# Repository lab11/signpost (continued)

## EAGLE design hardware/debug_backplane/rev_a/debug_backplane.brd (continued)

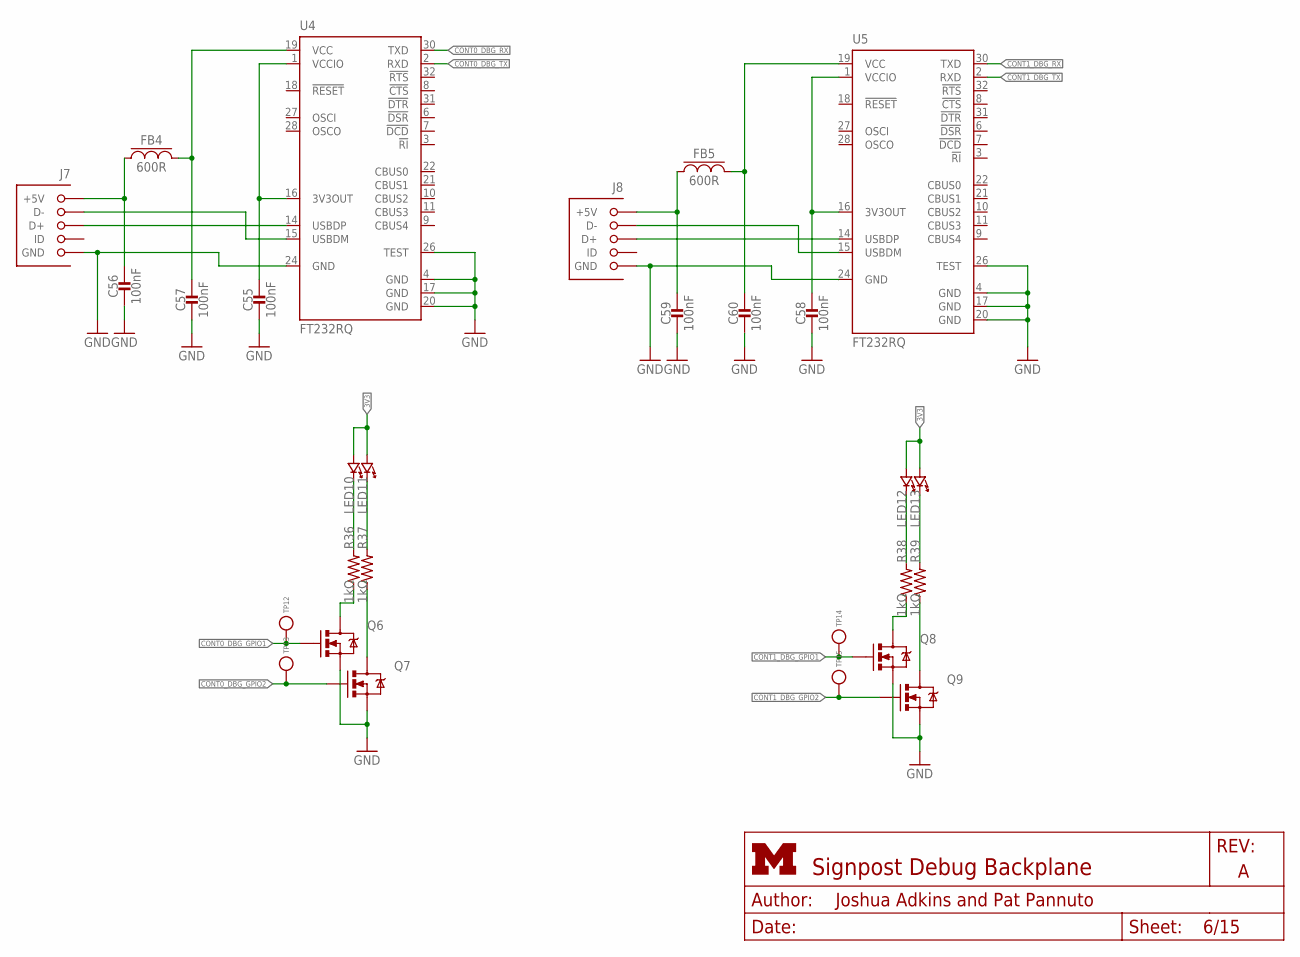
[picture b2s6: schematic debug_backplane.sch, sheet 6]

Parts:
C55, C56, C57, C58, C59, C60: 100nF; 0603_CAP
FB4, FB5: 600R; 0603_CAP
J7, J8: MICRO_USB_B_HIROSE_ZX62R-B-5P; USB_MICRO_B-HIROSE-ZX62R-B-5P
LED10, LED11, LED12, LED13: LED0603; LED-0603
Q6, Q7, Q8, Q9: MOSFET-NCHANNELSMD; SOT23-3
R36, R37, R38, R39: 1kΩ; 0603-RES
TP12, TP13, TP14, TP15: TEST_POINT_0.040IN; TESTPOINT_0.040IN
U4, U5: FT232RQ; QFN32

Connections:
3V3: LED10.A (ANODE), LED11.A (ANODE), LED12.A (ANODE), LED13.A (ANODE); also elsewhere on the board
CONT0_DBG_GPIO1: Q6.1 (G), TP12.TESTPOINT; also elsewhere on the board
CONT0_DBG_GPIO2: Q7.1 (G), TP13.TESTPOINT; also elsewhere on the board
CONT0_DBG_RX: U4.30 (TXD); also elsewhere on the board
CONT0_DBG_TX: U4.2 (RXD); also elsewhere on the board
CONT0_VCCIO: C55.1, U4.1 (VCCIO), U4.16 (3V3OUT)
CONT1_DBG_GPIO1: Q8.1 (G), TP14.TESTPOINT; also elsewhere on the board
CONT1_DBG_GPIO2: Q9.1 (G), TP15.TESTPOINT; also elsewhere on the board
CONT1_DBG_RX: U5.30 (TXD); also elsewhere on the board
CONT1_DBG_TX: U5.2 (RXD); also elsewhere on the board
CONT1_VCCIO: C58.1, U5.1 (VCCIO), U5.16 (3V3OUT)
GND: C55.2, C56.2, C57.2, C58.2, C59.2, C60.2, J7.5 (GND), J8.5 (GND), Q6.2 (S), Q7.2 (S), Q8.2 (S), Q9.2 (S), U4.4 (GND), U4.17 (GND), U4.20 (GND), U4.24 (GND), U4.26 (TEST), U5.4 (GND), U5.17 (GND), U5.20 (GND), U5.24 (GND), U5.26 (TEST); also elsewhere on the board
unnamed: J7.2 (D-), U4.15 (USBDM)
unnamed: J7.3 (D+), U4.14 (USBDP)
unnamed: C56.1, FB4.1, J7.1 (+5V)
unnamed: C57.1, FB4.2, U4.19 (VCC)
unnamed: J8.2 (D-), U5.15 (USBDM)
unnamed: J8.3 (D+), U5.14 (USBDP)
unnamed: C59.1, FB5.1, J8.1 (+5V)
unnamed: C60.1, FB5.2, U5.19 (VCC)
unnamed: LED10.C (CATHODE), R36.2
unnamed: LED11.C (CATHODE), R37.2
unnamed: Q6.3 (D), R36.1
unnamed: Q7.3 (D), R37.1
unnamed: LED12.C (CATHODE), R38.2
unnamed: LED13.C (CATHODE), R39.2
unnamed: Q8.3 (D), R38.1
unnamed: Q9.3 (D), R39.1

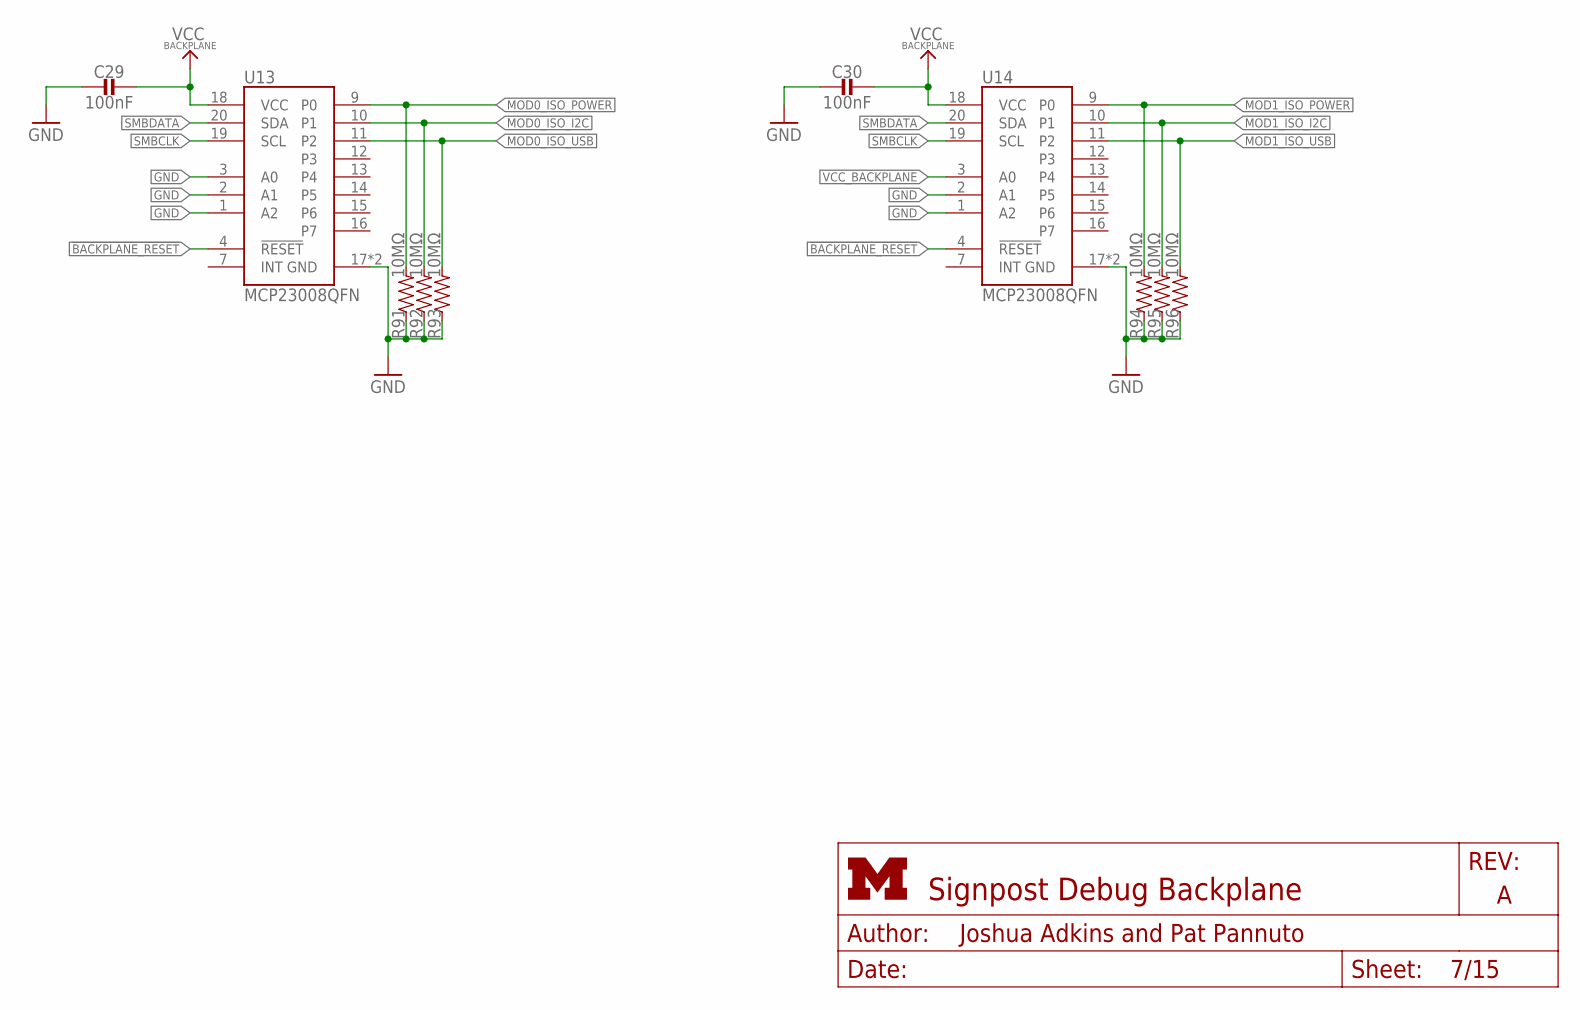
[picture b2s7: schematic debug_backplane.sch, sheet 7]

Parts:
C29, C30: 100nF; 0603_CAP
R91, R92, R93, R94, R95, R96: 10MΩ; 0603-RES
U13, U14: MCP23008QFN; QFN-20-4MM

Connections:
!BACKPLANE_RESET: U13.4 (!RESET), U14.4 (!RESET); also elsewhere on the board
GND: C29.2, C30.2, R91.1, R92.1, R93.1, R94.1, R95.1, R96.1, U13.1 (A2), U13.2 (A1), U13.3 (A0), U13.17 (GND), U13.GND, U14.1 (A2), U14.2 (A1), U14.17 (GND), U14.GND; also elsewhere on the board
MOD0_ISO_I2C: R92.2, U13.10 (P1); also elsewhere on the board
MOD0_ISO_POWER: R91.2, U13.9 (P0); also elsewhere on the board
MOD0_ISO_USB: R93.2, U13.11 (P2); also elsewhere on the board
MOD1_ISO_I2C: R95.2, U14.10 (P1); also elsewhere on the board
MOD1_ISO_POWER: R94.2, U14.9 (P0); also elsewhere on the board
MOD1_ISO_USB: R96.2, U14.11 (P2); also elsewhere on the board
SMBCLK: U13.19 (SCL), U14.19 (SCL); also elsewhere on the board
SMBDATA: U13.20 (SDA), U14.20 (SDA); also elsewhere on the board
VCC_BACKPLANE: C29.1, C30.1, U13.18 (VCC), U14.3 (A0), U14.18 (VCC); also elsewhere on the board

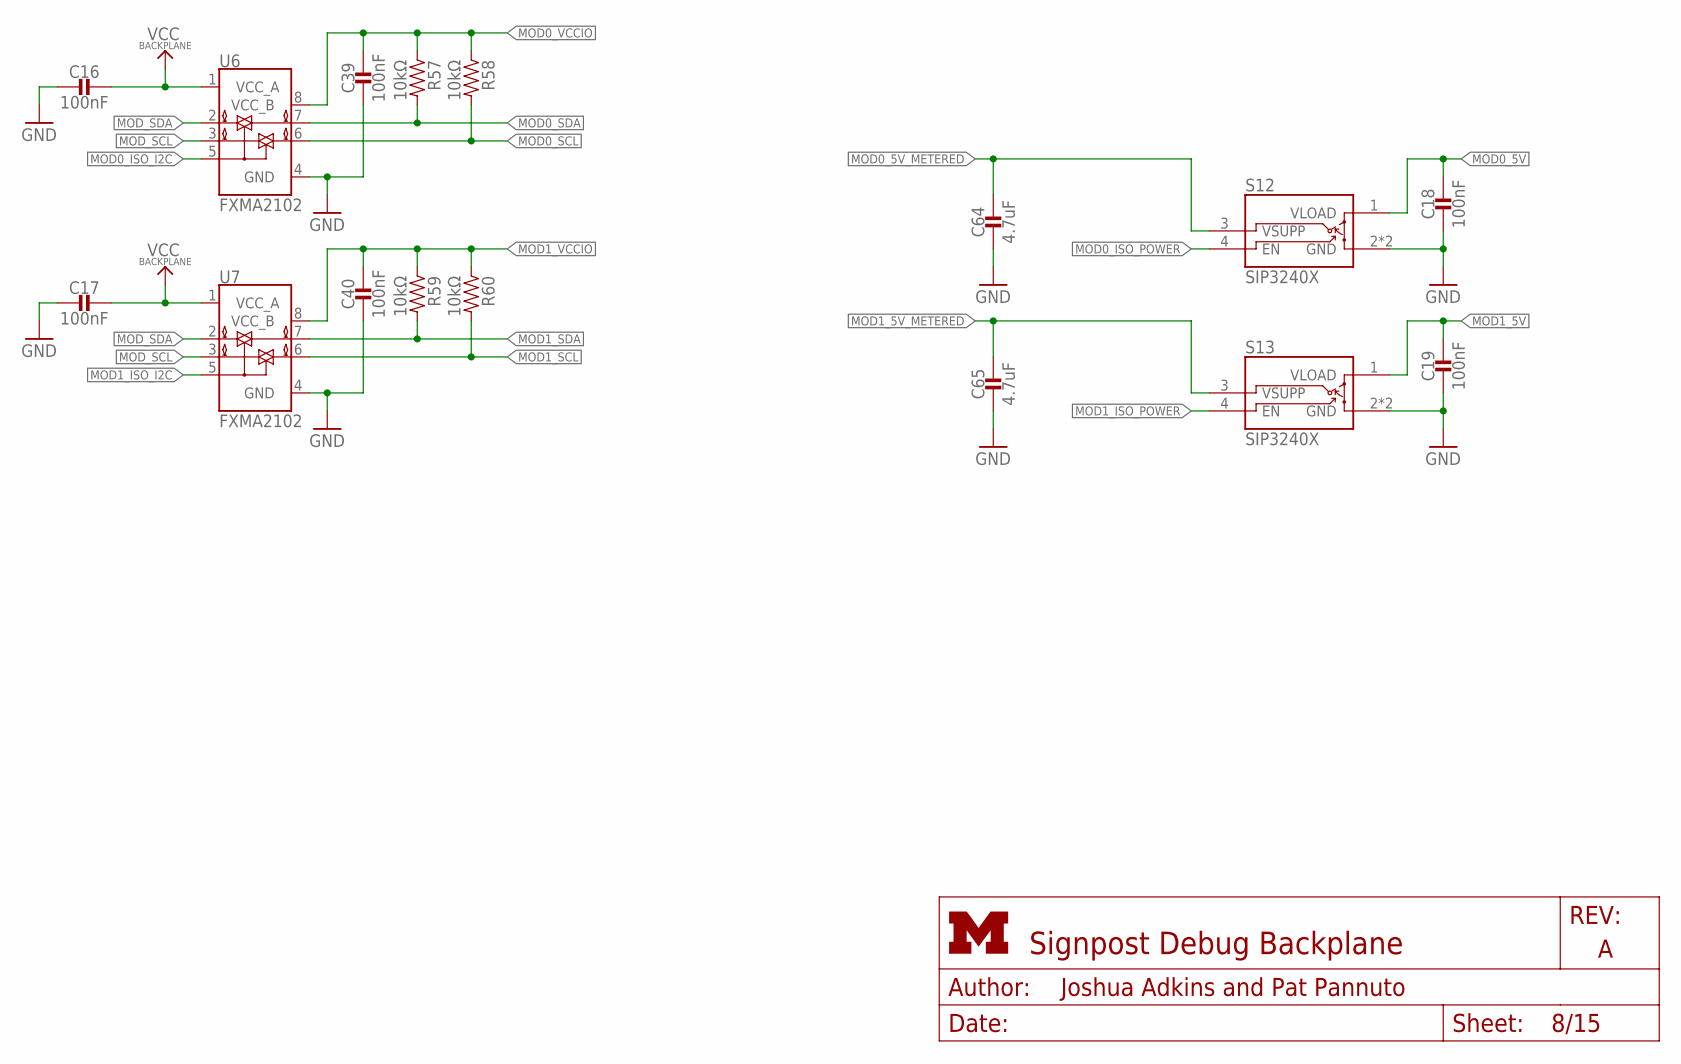
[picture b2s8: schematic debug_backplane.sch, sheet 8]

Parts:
C16, C17, C18, C19, C39, C40: 100nF; 0603_CAP
C64, C65: 4.7uF; 0603_CAP
R57, R58, R59, R60: 10kΩ; 0603-RES
S12, S13: SIP3240X; TDFN4
U6, U7: FXMA2102; UMLP-8

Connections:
GND: C16.2, C17.2, C18.2, C19.2, C39.2, C40.2, C64.2, C65.2, S12.2 (GND), S12.PAD (GND), S13.2 (GND), S13.PAD (GND), U6.4 (GND), U7.4 (GND); also elsewhere on the board
MOD0_5V: C18.1, S12.1 (VLOAD); also elsewhere on the board
MOD0_5V_METERED: C64.1, S12.3 (VSUPP); also elsewhere on the board
MOD0_ISO_I2C: U6.5 (OE); also elsewhere on the board
MOD0_ISO_POWER: S12.4 (EN); also elsewhere on the board
MOD0_SCL: R58.2, U6.6 (B1); also elsewhere on the board
MOD0_SDA: R57.2, U6.7 (B0); also elsewhere on the board
MOD0_VCCIO: C39.1, R57.1, R58.1, U6.8 (VCC_B); also elsewhere on the board
MOD1_5V: C19.1, S13.1 (VLOAD); also elsewhere on the board
MOD1_5V_METERED: C65.1, S13.3 (VSUPP); also elsewhere on the board
MOD1_ISO_I2C: U7.5 (OE); also elsewhere on the board
MOD1_ISO_POWER: S13.4 (EN); also elsewhere on the board
MOD1_SCL: R60.2, U7.6 (B1); also elsewhere on the board
MOD1_SDA: R59.2, U7.7 (B0); also elsewhere on the board
MOD1_VCCIO: C40.1, R59.1, R60.1, U7.8 (VCC_B); also elsewhere on the board
MOD_SCL: U6.3 (A1), U7.3 (A1); also elsewhere on the board
MOD_SDA: U6.2 (A0), U7.2 (A0); also elsewhere on the board
VCC_BACKPLANE: C16.1, C17.1, U6.1 (VCC_A), U7.1 (VCC_A); also elsewhere on the board

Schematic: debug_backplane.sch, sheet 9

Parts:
C20, C21, C22, C23, C24, C25, C26, C27: 100nF; 0603_CAP
U17, U18, U19, U20: SN74LVC2T45; VFSOP-8

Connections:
CONT_MOD0_IN: U17.2 (A1); also elsewhere on the board
CONT_MOD0_OUT: U19.2 (A1); also elsewhere on the board
CONT_MOD1_IN: U18.2 (A1); also elsewhere on the board
CONT_MOD1_OUT: U20.2 (A1); also elsewhere on the board
GND: C20.2, C21.2, C22.2, C23.2, C24.2, C25.2, C26.2, C27.2, U17.4 (GND), U18.4 (GND), U19.4 (GND), U19.5 (DIR), U20.4 (GND), U20.5 (DIR); also elsewhere on the board
MOD0_IN: U17.7 (B1); also elsewhere on the board
MOD0_OUT: U19.7 (B1); also elsewhere on the board
MOD0_PPS: U17.6 (B2); also elsewhere on the board
MOD0_VCCIO: C24.1, C26.1, U17.8 (VCC_B), U19.8 (VCC_B); also elsewhere on the board
MOD1_IN: U18.7 (B1); also elsewhere on the board
MOD1_OUT: U20.7 (B1); also elsewhere on the board
MOD1_PPS: U18.6 (B2); also elsewhere on the board
MOD1_VCCIO: C25.1, C27.1, U18.8 (VCC_B), U20.8 (VCC_B); also elsewhere on the board
PPS: U17.3 (A2), U18.3 (A2); also elsewhere on the board
VCC_BACKPLANE: C20.1, C21.1, C22.1, C23.1, U17.1 (VCC_A), U17.5 (DIR), U18.1 (VCC_A), U18.5 (DIR), U19.1 (VCC_A), U20.1 (VCC_A); also elsewhere on the board

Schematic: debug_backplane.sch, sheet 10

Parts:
C3, C4: 22pF; 0603_CAP; DIGIKEY 1276-1023-1-ND
C28: 100nF; 0603_CAP
C66: 4.7uF; 0603_CAP
R40, R41: 1.5kΩ; 0603-RES
R66, R67, R68, R69, R72: 10kΩ; 0603-RES
R79, R80, R81, R82, R83, R84, R85, R86: 15kΩ; 0603-RES
U24: TUSB2077A; LQFP-48
Y1: ABMM

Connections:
!BACKPLANE_RESET: U24.6 (!RESET); also elsewhere on the board
GND: C3.1, C4.1, C28.1, C66.1, R79.2, R80.2, R81.2, R82.2, R83.2, R84.2, R85.2, R86.2, U24.5 (GND), U24.10 (!BUSPWR), U24.24 (GND), U24.43 (GND), U24.48 (MODE); also elsewhere on the board
HUB_!OVRCUR1: U24.12 (!OVRCUR1); also elsewhere on the board
HUB_!OVRCUR2: U24.16 (!OVRCUR2); also elsewhere on the board
HUB_!OVRCUR3: R72.1, U24.20 (!OVRCUR3); also elsewhere on the board
HUB_!OVRCUR4: R67.1, U24.25 (!OVRCUR4)
HUB_!OVRCUR5: R66.1, U24.29 (!OVRCUR5)
HUB_!OVRCUR6: R68.1, U24.33 (!OVRCUR6)
HUB_!OVRCUR7: R69.1, U24.37 (!OVRCUR7)
HUB_!PWRON1: U24.11 (!PWRON1); also elsewhere on the board
HUB_!PWRON2: U24.15 (!PWRON2); also elsewhere on the board
HUB_!PWRON3: U24.19 (!PWRON3); also elsewhere on the board
HUB_!PWRON4: U24.23 (!PWRON4)
HUB_!PWRON5: U24.28 (!PWRON5)
HUB_!PWRON6: U24.32 (!PWRON6)
HUB_!PWRON7: U24.36 (!PWRON7)
HUB_CFG: U24.40 (HUBCFG); also elsewhere on the board
HUB_DM1: U24.13 (DM1); also elsewhere on the board
HUB_DM2: U24.17 (DM2); also elsewhere on the board
HUB_DM3: U24.21 (DM3); also elsewhere on the board
HUB_DM4: R82.1, U24.26 (DM4)
HUB_DM5: R80.1, U24.30 (DM5)
HUB_DM6: R84.1, U24.34 (DM6)
HUB_DM7: R86.1, U24.38 (DM7)
HUB_DP1: U24.14 (DP1); also elsewhere on the board
HUB_DP2: U24.18 (DP2); also elsewhere on the board
HUB_DP3: U24.22 (DP3); also elsewhere on the board
HUB_DP4: R81.1, U24.27 (DP4)
HUB_DP5: R79.1, U24.31 (DP5)
HUB_DP6: R83.1, U24.35 (DP6)
HUB_DP7: R85.1, U24.39 (DP7)
HUB_PORTDIS: U24.42 (PORTDIS); also elsewhere on the board
HUB_PORTPWR: U24.41 (PORTPWR); also elsewhere on the board
unnamed: R40.2, U24.2 (DP0PUR)
unnamed: C4.2, R41.1, Y1.1
unnamed: C3.2, U24.45 (XTAL1), Y1.3 (2)
unnamed: R41.2, U24.44 (XTAL2)
USB+: R40.1, U24.3 (DP0); also elsewhere on the board
USB-: U24.4 (DM0); also elsewhere on the board
USB_SUSPEND_STATUS: U24.1 (SUSPND); also elsewhere on the board
VCC_BACKPLANE: C28.2, C66.2, R66.2, R67.2, R68.2, R69.2, R72.2, U24.8 (EEDATA/!GANGED), U24.9 (VCC), U24.46 (VCC), U24.47 (!EXTMEM); also elsewhere on the board

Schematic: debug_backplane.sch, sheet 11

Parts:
C61: 100nF; 0603_CAP
J9: MICRO_USB_B_HIROSE_ZX62R-B-5P; USB_MICRO_B-HIROSE-ZX62R-B-5P
Q1: DMN32D2LDF; SOT353
R89, R90: 100kΩ; 0603-RES
U23: TS3USB30E; UQFN-10

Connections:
CONT_USB+: U23.2 (D2+); also elsewhere on the board
CONT_USB-: U23.6 (D2-); also elsewhere on the board
GND: C61.1, J9.5 (GND), Q1.S, R90.1, U23.4 (GND), U23.8 (!OE); also elsewhere on the board
unnamed: J9.1 (+5V), Q1.G2, R90.2
unnamed: Q1.D2, R89.1, U23.10 (S)
unnamed: J9.3 (D+), U23.1 (D1+)
unnamed: J9.2 (D-), U23.7 (D1-)
USB+: U23.3 (D+); also elsewhere on the board
USB-: U23.5 (D-); also elsewhere on the board
VCC_BACKPLANE: C61.2, R89.2, U23.9 (VCC); also elsewhere on the board

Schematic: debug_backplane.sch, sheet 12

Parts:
C5, C6, C7, C8, C9, C10: 22pF; 0402_CAP
C37, C38: 100nF; 0603_CAP
D7, D8: SN75240-TSSOP; TSSOP-8
R6, R7, R8, R9, R10, R11: 27Ω; 0402_RES-HIGH_SPEED
R12, R13, R14, R15: 50Ω; 0603-RES
R73, R74, R75, R76, R77, R78: 15kΩ; 0603-RES
U21, U22: TS3USB30E; UQFN-10

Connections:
GND: C5.2, C6.2, C7.2, C8.2, C9.2, C10.2, C37.1, C38.1, D7.1 (GND), D7.3 (GND), D7.5 (GND), D7.7 (GND), D8.1 (GND), D8.3 (GND), D8.5 (GND), D8.7 (GND), R12.2, R13.2, R14.2, R15.2, R73.1, R74.1, R75.1, R76.1, R77.1, R78.1, U21.4 (GND), U21.10 (S), U22.4 (GND), U22.10 (S); also elsewhere on the board
HUB_DM1: C8.1, R9.2; also elsewhere on the board
HUB_DM2: C6.1, R7.2; also elsewhere on the board
HUB_DM3: C10.1, R11.2; also elsewhere on the board
HUB_DP1: C7.1, R8.2; also elsewhere on the board
HUB_DP2: C5.1, R6.2; also elsewhere on the board
HUB_DP3: C9.1, R10.2; also elsewhere on the board
MOD0_D+_HUB-SW: D8.4 (D), R6.1, R73.2, U21.3 (D+)
MOD0_D-_HUB-SW: D8.2 (C), R7.1, R74.2, U21.5 (D-)
MOD0_USB+: U21.1 (D1+); also elsewhere on the board
MOD0_USB-: U21.7 (D1-); also elsewhere on the board
MOD0_USB_!EN: U21.8 (!OE); also elsewhere on the board
MOD1_D+_HUB-SW: D8.8 (A), R8.1, R75.2, U22.3 (D+)
MOD1_D-_HUB-SW: D8.6 (B), R9.1, R76.2, U22.5 (D-)
MOD1_USB+: U22.1 (D1+); also elsewhere on the board
MOD1_USB-: U22.7 (D1-); also elsewhere on the board
MOD1_USB_!EN: U22.8 (!OE); also elsewhere on the board
MOD2_USB+: D7.8 (A), R10.1, R77.2; also elsewhere on the board
MOD2_USB-: D7.6 (B), R11.1, R78.2; also elsewhere on the board
unnamed: R12.1, U21.2 (D2+)
unnamed: R15.1, U22.6 (D2-)
unnamed: R14.1, U22.2 (D2+)
unnamed: R13.1, U21.6 (D2-)
VCC_BACKPLANE: C37.2, C38.2, U21.9 (VCC), U22.9 (VCC); also elsewhere on the board

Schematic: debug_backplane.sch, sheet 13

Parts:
C31, C32, C33, C34, C35, C36: 100nF; 0603_CAP
C68, C69: 150uF; 1210_CAP; DIGIKEY 1276-3367-1-ND
R55, R56: 10kΩ; 0603-RES
S1, S2: AP2401MP; MSOP-8EP
S9, S10: NC7SZ157; SC70-6

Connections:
GND: C31.2, C32.2, C33.2, C34.2, C35.2, C36.2, C68.2, C69.2, S1.1 (GND), S1.PAD (GND), S2.1 (GND), S2.PAD (GND), S9.2 (GND), S10.2 (GND); also elsewhere on the board
HUB_!OVRCUR1: R56.1, S2.5 (!FLG); also elsewhere on the board
HUB_!OVRCUR2: R55.1, S1.5 (!FLG); also elsewhere on the board
HUB_!PWRON1: S10.1 (I1); also elsewhere on the board
HUB_!PWRON2: S9.1 (I1); also elsewhere on the board
MOD0_5V_METERED: C35.1, S1.2 (IN), S1.3 (IN); also elsewhere on the board
MOD0_ISO_USB: S9.6 (S); also elsewhere on the board
MOD0_USB_!EN: S1.4 (!EN), S9.4 (Z); also elsewhere on the board
MOD0_USB_VBUS: C31.1, C68.1, S1.6 (OUT), S1.7 (OUT); also elsewhere on the board
MOD1_5V_METERED: C36.1, S2.2 (IN), S2.3 (IN); also elsewhere on the board
MOD1_ISO_USB: S10.6 (S); also elsewhere on the board
MOD1_USB_!EN: S2.4 (!EN), S10.4 (Z); also elsewhere on the board
MOD1_USB_VBUS: C32.1, C69.1, S2.6 (OUT), S2.7 (OUT); also elsewhere on the board
VCC_BACKPLANE: C33.1, C34.1, R55.2, R56.2, S9.3 (I0), S9.5 (VCC), S10.3 (I0), S10.5 (VCC); also elsewhere on the board

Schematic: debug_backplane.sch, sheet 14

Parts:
C1, C2: 8pF; 0603_CAP; DIGIKEY 490-8230-1-ND
C41, C42, C43, C44, C46, C47, C48: 100nF; 0603_CAP; DIGIKEY 490-10777-1-ND
C45: 100nF; 0402_CAP; DIGIKEY 490-10777-1-ND
C67: 4.7uF; 0402_CAP; DIGIKEY 490-13252-1-ND
FB1: 600R; 0603_CAP
FB6: 1.5kR; 0603_CAP; DIGIKEY 490-5216-1-ND
J4: MICRO_USB_B_HIROSE_ZX62R-B-5P; USB_MICRO_B-HIROSE-ZX62R-B-5P
L1: 22uH; 1212
R1: 0Ω; 0603-RES; DIGIKEY 1276-3431-1-ND
R71: 10kΩ; 0603-RES; DIGIKEY 1276-3431-1-ND
R87, R88: 100kΩ; 0603-RES; DIGIKEY 1276-3432-1-ND
S3: B3U-1000P
TP54: TEST_POINT_0.040IN; TESTPOINT_0.040IN
U1: FT232RQ; QFN32
U16: SAM4LC8AA; QFN-48-7MM
X1: 16MHz; FHXXX

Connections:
3V3: C42.1, C43.1, C44.1, FB6.2, R71.2, R87.2, R88.2, U16.8 (VDDIN), U16.27 (VLCD), U16.31 (VLCDIN), U16.40 (VDDIO), U16.45 (VDDIO); also elsewhere on the board
CONTROLLER_BUCK/LDO_N: R1.2, R71.1, U16.3 (PA02)
CONTROLLER_XIN: C1.1, U16.1 (PA00), X1.3 (2)
CONTROLLER_XOUT: C2.1, U16.2 (PA01), X1.1
CONT_MOD2_IN: U16.39 (PA20); also elsewhere on the board
CONT_MOD2_OUT: U16.38 (PA19); also elsewhere on the board
GND: C1.2, C2.2, C41.2, C42.2, C43.2, C44.2, C45.2, C46.2, C47.2, C48.2, C67.2, J4.5 (GND), R1.1, S3.1, TP54.TESTPOINT, U1.4 (GND), U1.17 (GND), U1.20 (GND), U1.24 (GND), U1.26 (TEST), U16.6 (GND), U16.17 (GNDANA), U16.30 (GND), U16.48 (GND), U16.THERMAL (GND), X1.2 (GND), X1.4 (GND); also elsewhere on the board
MOD2_USB+: U16.47 (PA26); also elsewhere on the board
MOD2_USB-: U16.46 (PA25); also elsewhere on the board
MOD_SCL: U16.44 (PA24); also elsewhere on the board
MOD_SDA: U16.43 (PA23); also elsewhere on the board
unnamed: C41.1, FB6.1, U16.19 (VDDANA)
unnamed: L1.P$2 (2), U16.5 (VDDCORE)
unnamed: U16.28 (BIASH), U16.29 (BIASL)
unnamed: U16.25 (CAPH), U16.26 (CAPL)
unnamed: J4.2 (D-), U1.15 (USBDM)
unnamed: C45.1, C67.1, L1.P$1 (1), U16.7 (VDDOUT)
unnamed: J4.3 (D+), U1.14 (USBDP)
unnamed: C46.1, FB1.2, J4.1 (+5V)
unnamed: C47.1, FB1.1, U1.19 (VCC)
unnamed: C48.1, U1.1 (VCCIO), U1.16 (3V3OUT)
PPS: U16.37 (PA18); also elsewhere on the board
RADIO_!RESET: S3.2, U16.4 (!RESET); also elsewhere on the board
RADIO_RX: U1.30 (TXD), U16.23 (PA11)
RADIO_SWDCLK: R88.1, U16.9 (TCK); also elsewhere on the board
RADIO_SWDIO: R87.1, U16.10 (PA03); also elsewhere on the board
RADIO_TX: U1.2 (RXD), U16.24 (PA12)

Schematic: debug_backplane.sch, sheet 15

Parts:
D1, D2, D3, D4, D5, D6: LED0603; LED-0603
R16, R17, R18, R19, R20, R21: 1kΩ; 0603-RES
TP1, TP2, TP3, TP4, TP5, TP6, TP7, TP8, TP9, TP10, TP11, TP16, TP17, TP18, TP20, TP23, TP24, TP25, TP27, TP28, TP29, TP30, TP31, TP32, TP33, TP34, TP35, TP36, TP37, TP41, TP42, TP43, TP44, TP45, TP46, TP47, TP48, TP49, TP50, TP51, TP52, TP53, TP55, TP56, TP57, TP58, TP1001, TP1002, TP1003, TP1004, TP1005, TP1006: TEST_POINT_0.040IN; TESTPOINT_0.040IN

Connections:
3V3: TP7.TESTPOINT; also elsewhere on the board
5V: TP4.TESTPOINT; also elsewhere on the board
!BACKPLANE_RESET: TP9.TESTPOINT; also elsewhere on the board
!SMBALERT: TP3.TESTPOINT; also elsewhere on the board
GND: R16.1, R17.1, R18.1, R19.1, R20.1, R21.1, TP11.TESTPOINT, TP25.TESTPOINT, TP27.TESTPOINT, TP51.TESTPOINT, TP56.TESTPOINT; also elsewhere on the board
HUB_!OVRCUR1: TP33.TESTPOINT; also elsewhere on the board
HUB_!OVRCUR2: TP35.TESTPOINT; also elsewhere on the board
HUB_!OVRCUR3: TP37.TESTPOINT; also elsewhere on the board
HUB_!PWRON1: TP32.TESTPOINT; also elsewhere on the board
HUB_!PWRON2: TP34.TESTPOINT; also elsewhere on the board
HUB_!PWRON3: TP36.TESTPOINT; also elsewhere on the board
HUB_CFG: TP28.TESTPOINT; also elsewhere on the board
HUB_PORTDIS: TP30.TESTPOINT; also elsewhere on the board
HUB_PORTPWR: TP29.TESTPOINT; also elsewhere on the board
MOD0_5V: TP57.TESTPOINT; also elsewhere on the board
MOD0_5V_METERED: TP16.TESTPOINT; also elsewhere on the board
MOD0_IN: TP48.TESTPOINT; also elsewhere on the board
MOD0_ISO_I2C: D2.A (ANODE), TP1002.TESTPOINT; also elsewhere on the board
MOD0_ISO_POWER: D1.A (ANODE), TP1001.TESTPOINT; also elsewhere on the board
MOD0_ISO_USB: D3.A (ANODE), TP1003.TESTPOINT; also elsewhere on the board
MOD0_OUT: TP49.TESTPOINT; also elsewhere on the board
MOD0_PPS: TP46.TESTPOINT; also elsewhere on the board
MOD0_SCL: TP43.TESTPOINT; also elsewhere on the board
MOD0_SDA: TP42.TESTPOINT; also elsewhere on the board
MOD0_USB_VBUS: TP20.TESTPOINT; also elsewhere on the board
MOD0_VCCIO: TP50.TESTPOINT; also elsewhere on the board
MOD1_5V: TP58.TESTPOINT; also elsewhere on the board
MOD1_5V_METERED: TP17.TESTPOINT; also elsewhere on the board
MOD1_IN: TP52.TESTPOINT; also elsewhere on the board
MOD1_ISO_I2C: D5.A (ANODE), TP1005.TESTPOINT; also elsewhere on the board
MOD1_ISO_POWER: D4.A (ANODE), TP1004.TESTPOINT; also elsewhere on the board
MOD1_ISO_USB: D6.A (ANODE), TP1006.TESTPOINT; also elsewhere on the board
MOD1_OUT: TP53.TESTPOINT; also elsewhere on the board
MOD1_PPS: TP47.TESTPOINT; also elsewhere on the board
MOD1_SCL: TP45.TESTPOINT; also elsewhere on the board
MOD1_SDA: TP44.TESTPOINT; also elsewhere on the board
MOD1_USB_VBUS: TP41.TESTPOINT; also elsewhere on the board
MOD1_VCCIO: TP55.TESTPOINT; also elsewhere on the board
MOD_SCL: TP6.TESTPOINT; also elsewhere on the board
MOD_SDA: TP5.TESTPOINT; also elsewhere on the board
unnamed: D1.C (CATHODE), R16.2
unnamed: D2.C (CATHODE), R18.2
unnamed: D3.C (CATHODE), R17.2
unnamed: D4.C (CATHODE), R19.2
unnamed: D5.C (CATHODE), R20.2
unnamed: D6.C (CATHODE), R21.2
PPS: TP10.TESTPOINT; also elsewhere on the board
SMBCLK: TP2.TESTPOINT; also elsewhere on the board
SMBDATA: TP1.TESTPOINT; also elsewhere on the board
USB_SUSPEND_STATUS: TP31.TESTPOINT; also elsewhere on the board
VCC_BACKPLANE: TP8.TESTPOINT, TP24.TESTPOINT; also elsewhere on the board
VCC_LINUX: TP18.TESTPOINT, TP23.TESTPOINT; also elsewhere on the board

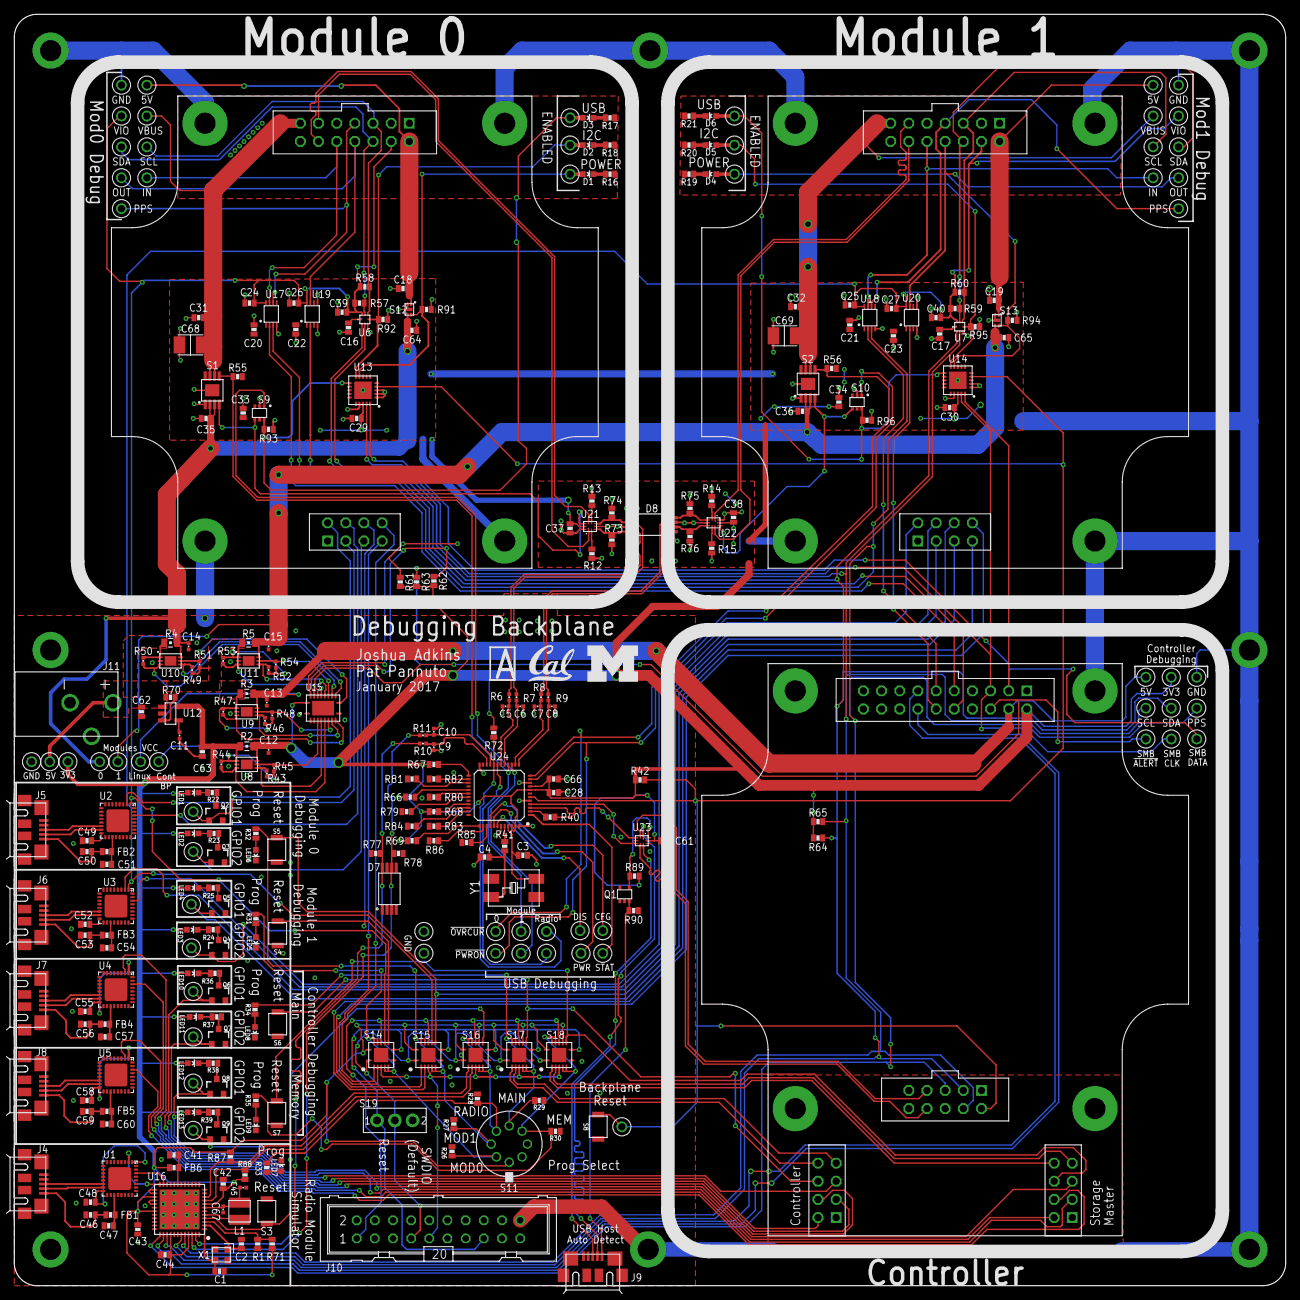
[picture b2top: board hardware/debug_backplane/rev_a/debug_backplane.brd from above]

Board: 2 copper layers, 177.8 x 177.8 mm, 321 parts (0 on the bottom side), 214 nets.

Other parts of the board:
U$12: UMICH_SOLID_200MIL
U$15: UCB_CAL_200MIL

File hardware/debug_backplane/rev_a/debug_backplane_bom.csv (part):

"# Bill of Materials",,,,,,,,,,,
"# Converted from debug_backplane_bom.xlsx",,,,,,,,,,,
"# Generated by bom_to_text.py",,,,,,,,,,,
"#",,,,,,,,,,,
Part,Value,Device,Package,Description,DIGIKEY,MF,MOUSER,MPN,NEWARK,OC_FARNELL,OC_NEWARK
C1,8pF,CAPACITOR0603_CAP,0603_CAP,0402 Capacitor,1276-2141-1-ND,,,,,,
C2,8pF,CAPACITOR0603_CAP,0603_CAP,0402 Capacitor,1276-2141-1-ND,,,,,,
C3,22pF,CAPACITOR0603_CAP,0603_CAP,0402 Capacitor,478-1167-1-ND,,,,,,
C4,22pF,CAPACITOR0603_CAP,0603_CAP,0402 Capacitor,478-1167-1-ND,,,,,,
C5,22pF,CAPACITOR0402_CAP,0402_CAP,0402 Capacitor,399-8827-1-ND,,,,,,
C6,22pF,CAPACITOR0402_CAP,0402_CAP,0402 Capacitor,399-8827-1-ND,,,,,,
C7,22pF,CAPACITOR0402_CAP,0402_CAP,0402 Capacitor,399-8827-1-ND,,,,,,
C8,22pF,CAPACITOR0402_CAP,0402_CAP,0402 Capacitor,399-8827-1-ND,,,,,,
C9,22pF,CAPACITOR0402_CAP,0402_CAP,0402 Capacitor,399-8827-1-ND,,,,,,
C10,22pF,CAPACITOR0402_CAP,0402_CAP,0402 Capacitor,399-8827-1-ND,,,,,,
C11,0.01uF,CAPACITOR0402_CAP,0402_CAP,0402 Capacitor,490-1313-1-ND,,,,,,
C12,0.1uF,CAPACITOR0402_CAP,0402_CAP,0402 Capacitor,478-1129-1-ND,,,,,,
C13,0.1uF,CAPACITOR0402_CAP,0402_CAP,0402 Capacitor,478-1129-1-ND,,,,,,
C14,0.1uF,CAPACITOR0402_CAP,0402_CAP,0402 Capacitor,478-1129-1-ND,,,,,,
C15,0.1uF,CAPACITOR0402_CAP,0402_CAP,0402 Capacitor,478-1129-1-ND,,,,,,
C16,100nF,CAPACITOR0603_CAP,0603_CAP,0402 Capacitor,490-1532-1-ND,,,,,,
C17,100nF,CAPACITOR0603_CAP,0603_CAP,0402 Capacitor,490-1532-1-ND,,,,,,
C18,100nF,CAPACITOR0603_CAP,0603_CAP,0402 Capacitor,490-1532-1-ND,,,,,,
C19,100nF,CAPACITOR0603_CAP,0603_CAP,0402 Capacitor,490-1532-1-ND,,,,,,
C20,100nF,CAPACITOR0603_CAP,0603_CAP,0402 Capacitor,490-1532-1-ND,,,,,,
C21,100nF,CAPACITOR0603_CAP,0603_CAP,0402 Capacitor,490-1532-1-ND,,,,,,
C22,100nF,CAPACITOR0603_CAP,0603_CAP,0402 Capacitor,490-1532-1-ND,,,,,,
C23,100nF,CAPACITOR0603_CAP,0603_CAP,0402 Capacitor,490-1532-1-ND,,,,,,
C24,100nF,CAPACITOR0603_CAP,0603_CAP,0402 Capacitor,490-1532-1-ND,,,,,,
C25,100nF,CAPACITOR0603_CAP,0603_CAP,0402 Capacitor,490-1532-1-ND,,,,,,
C26,100nF,CAPACITOR0603_CAP,0603_CAP,0402 Capacitor,490-1532-1-ND,,,,,,
C27,100nF,CAPACITOR0603_CAP,0603_CAP,0402 Capacitor,490-1532-1-ND,,,,,,
C28,100nF,CAPACITOR0603_CAP,0603_CAP,0402 Capacitor,490-1532-1-ND,,,,,,
C29,100nF,CAPACITOR0603_CAP,0603_CAP,0402 Capacitor,490-1532-1-ND,,,,,,
C30,100nF,CAPACITOR0603_CAP,0603_CAP,0402 Capacitor,490-1532-1-ND,,,,,,
C31,100nF,CAPACITOR0603_CAP,0603_CAP,0402 Capacitor,490-1532-1-ND,,,,,,
C32,100nF,CAPACITOR0603_CAP,0603_CAP,0402 Capacitor,490-1532-1-ND,,,,,,
C33,100nF,CAPACITOR0603_CAP,0603_CAP,0402 Capacitor,490-1532-1-ND,,,,,,
C34,100nF,CAPACITOR0603_CAP,0603_CAP,0402 Capacitor,490-1532-1-ND,,,,,,
C35,100nF,CAPACITOR0603_CAP,0603_CAP,0402 Capacitor,490-1532-1-ND,,,,,,
C36,100nF,CAPACITOR0603_CAP,0603_CAP,0402 Capacitor,490-1532-1-ND,,,,,,
C37,100nF,CAPACITOR0603_CAP,0603_CAP,0402 Capacitor,490-1532-1-ND,,,,,,
C38,100nF,CAPACITOR0603_CAP,0603_CAP,0402 Capacitor,490-1532-1-ND,,,,,,
C39,100nF,CAPACITOR0603_CAP,0603_CAP,0402 Capacitor,490-1532-1-ND,,,,,,
C40,100nF,CAPACITOR0603_CAP,0603_CAP,0402 Capacitor,490-1532-1-ND,,,,,,
C41,100nF,CAPACITOR0603_CAP,0603_CAP,0402 Capacitor,490-1532-1-ND,,,,,,
C42,100nF,CAPACITOR0603_CAP,0603_CAP,0402 Capacitor,490-1532-1-ND,,,,,,
C43,100nF,CAPACITOR0603_CAP,0603_CAP,0402 Capacitor,490-1532-1-ND,,,,,,
C44,100nF,CAPACITOR0603_CAP,0603_CAP,0402 Capacitor,490-1532-1-ND,,,,,,
C45,100nF,CAPACITOR0402_CAP,0402_CAP,0402 Capacitor,478-1129-1-ND,,,,,,
C46,100nF,CAPACITOR0603_CAP,0603_CAP,0402 Capacitor,490-1532-1-ND,,,,,,
C47,100nF,CAPACITOR0603_CAP,0603_CAP,0402 Capacitor,490-1532-1-ND,,,,,,
C48,100nF,CAPACITOR0603_CAP,0603_CAP,0402 Capacitor,490-1532-1-ND,,,,,,
C49,100nF,CAPACITOR0603_CAP,0603_CAP,0402 Capacitor,490-1532-1-ND,,,,,,
C50,100nF,CAPACITOR0603_CAP,0603_CAP,0402 Capacitor,490-1532-1-ND,,,,,,
C51,100nF,CAPACITOR0603_CAP,0603_CAP,0402 Capacitor,490-1532-1-ND,,,,,,
C52,100nF,CAPACITOR0603_CAP,0603_CAP,0402 Capacitor,490-1532-1-ND,,,,,,
C53,100nF,CAPACITOR0603_CAP,0603_CAP,0402 Capacitor,490-1532-1-ND,,,,,,
C54,100nF,CAPACITOR0603_CAP,0603_CAP,0402 Capacitor,490-1532-1-ND,,,,,,
C55,100nF,CAPACITOR0603_CAP,0603_CAP,0402 Capacitor,490-1532-1-ND,,,,,,
C56,100nF,CAPACITOR0603_CAP,0603_CAP,0402 Capacitor,490-1532-1-ND,,,,,,
C57,100nF,CAPACITOR0603_CAP,0603_CAP,0402 Capacitor,490-1532-1-ND,,,,,,
C58,100nF,CAPACITOR0603_CAP,0603_CAP,0402 Capacitor,490-1532-1-ND,,,,,,
C59,100nF,CAPACITOR0603_CAP,0603_CAP,0402 Capacitor,490-1532-1-ND,,,,,,
C60,100nF,CAPACITOR0603_CAP,0603_CAP,0402 Capacitor,490-1532-1-ND,,,,,,
C61,100nF,CAPACITOR0603_CAP,0603_CAP,0402 Capacitor,490-1532-1-ND,,,,,,
C62,2.2uF,CAPACITOR0603_CAP,0603_CAP,0402 Capacitor,490-3296-1-ND,,,,,,
C63,2.2uF,CAPACITOR0603_CAP,0603_CAP,0402 Capacitor,490-3296-1-ND,,,,,,
C64,4.7uF,CAPACITOR0603_CAP,0603_CAP,0402 Capacitor,490-3297-1-ND,,,,,,
C65,4.7uF,CAPACITOR0603_CAP,0603_CAP,0402 Capacitor,490-3297-1-ND,,,,,,
C66,4.7uF,CAPACITOR0603_CAP,0603_CAP,0402 Capacitor,490-3297-1-ND,,,,,,
C67,4.7uF,CAPACITOR0402_CAP,0402_CAP,0402 Capacitor,490-5915-1-ND,,,,,,
C68,150uF,CAPACITOR1210_CAP,1210_CAP,0402 Capacitor,1276-3367-1-ND,,,,,,
C69,150uF,CAPACITOR1210_CAP,1210_CAP,0402 Capacitor,1276-3367-1-ND,,,,,,
D1,LED0603,LED0603,LED-0603,LED,160-1446-1-ND,,,,,,
D2,LED0603,LED0603,LED-0603,LED,160-1446-1-ND,,,,,,
D3,LED0603,LED0603,LED-0603,LED,160-1446-1-ND,,,,,,
D4,LED0603,LED0603,LED-0603,LED,160-1446-1-ND,,,,,,
D5,LED0603,LED0603,LED-0603,LED,160-1446-1-ND,,,,,,
D6,LED0603,LED0603,LED-0603,LED,160-1446-1-ND,,,,,,
D7,SN75240-TSSOP,SN75240-TSSOP,TSSOP-8,TVS Diodes [suggested for TI USB Hub] (2 array),296-6596-1-ND,,,,,,
D8,SN75240-TSSOP,SN75240-TSSOP,TSSOP-8,TVS Diodes [suggested for TI USB Hub] (2 array),296-6596-1-ND,,,,,,
FB1,600R,FERRITE_BEAD0603,0603_CAP,,732-1593-1-ND,,,,,,
FB2,600R,FERRITE_BEAD0603,0603_CAP,,732-1593-1-ND,,,,,,
FB3,600R,FERRITE_BEAD0603,0603_CAP,,732-1593-1-ND,,,,,,
FB4,600R,FERRITE_BEAD0603,0603_CAP,,732-1593-1-ND,,,,,,
FB5,600R,FERRITE_BEAD0603,0603_CAP,,732-1593-1-ND,,,,,,
FB6,1.5kR,FERRITE_BEAD0603,0603_CAP,,490-5216-1-ND,,,,,,
J1,BACKPLANE_CONTROLLER_MODULE_DEBUG,BACKPLANE_CONTROLLER_MODULE_DEBUG,BACKPLANE_MODULE_20PIN_10PIN_DEBUG,"Control module for signpost, with debug headers","S9197-ND , S9194-ND , S7072-ND , S7072-ND",,,,,,
J2,BACKPLANE_GENERIC_MODULE_DEBUG,BACKPLANE_GENERIC_MODULE_DEBUG,BACKPLANE_MODULE_14PIN_8PIN,A backplane header for the debug module,"S9195-ND , S7072-ND",,,,,,
J3,BACKPLANE_GENERIC_MODULE_DEBUG,BACKPLANE_GENERIC_MODULE_DEBUG,BACKPLANE_MODULE_14PIN_8PIN,A backplane header for the debug module,"S9195-ND , S7072-ND",,,,,,
J4,MICRO_USB_B_HIROSE_ZX62R-B-5P,MICRO_USB_B_HIROSE_ZX62R-B-5P,USB_MICRO_B-HIROSE-ZX62R-B-5P,USB Micro B Connector,H125274CT-ND,,798-ZX62R-B-5P,,69W0714,,
J5,MICRO_USB_B_HIROSE_ZX62R-B-5P,MICRO_USB_B_HIROSE_ZX62R-B-5P,USB_MICRO_B-HIROSE-ZX62R-B-5P,USB Micro B Connector,H125274CT-ND,,798-ZX62R-B-5P,,69W0714,,
J6,MICRO_USB_B_HIROSE_ZX62R-B-5P,MICRO_USB_B_HIROSE_ZX62R-B-5P,USB_MICRO_B-HIROSE-ZX62R-B-5P,USB Micro B Connector,H125274CT-ND,,798-ZX62R-B-5P,,69W0714,,
J7,MICRO_USB_B_HIROSE_ZX62R-B-5P,MICRO_USB_B_HIROSE_ZX62R-B-5P,USB_MICRO_B-HIROSE-ZX62R-B-5P,USB Micro B Connector,H125274CT-ND,,798-ZX62R-B-5P,,69W0714,,
J8,MICRO_USB_B_HIROSE_ZX62R-B-5P,MICRO_USB_B_HIROSE_ZX62R-B-5P,USB_MICRO_B-HIROSE-ZX62R-B-5P,USB Micro B Connector,H125274CT-ND,,798-ZX62R-B-5P,,69W0714,,
J9,MICRO_USB_B_HIROSE_ZX62R-B-5P,MICRO_USB_B_HIROSE_ZX62R-B-5P,USB_MICRO_B-HIROSE-ZX62R-B-5P,USB Micro B Connector,H125274CT-ND,,798-ZX62R-B-5P,,69W0714,,
J10,20 Pin JTAG Header,ML20,ML20,HARTING,S9172-ND,,,,,unknown,unknown
J11,PJ-102AH,PJ-102AH,PJ-102AH,DC Power Jack,CP-102AH-ND,,,,,,
L1,22uH,LHQ3NP,1212,LHQ3NP Inductor,490-5350-1-ND,,,,,,
LED1,LED0603,LED0603,LED-0603,LED,160-1447-1-ND,,,,,,
LED2,LED0603,LED0603,LED-0603,LED,160-1446-1-ND,,,,,,
LED3,LED0603,LED0603,LED-0603,LED,160-1447-1-ND,,,,,,
LED4,LED0603,LED0603,LED-0603,LED,160-1446-1-ND,,,,,,
LED5,LED0603,LED0603,LED-0603,LED,160-1827-1-ND,,,,,,
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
